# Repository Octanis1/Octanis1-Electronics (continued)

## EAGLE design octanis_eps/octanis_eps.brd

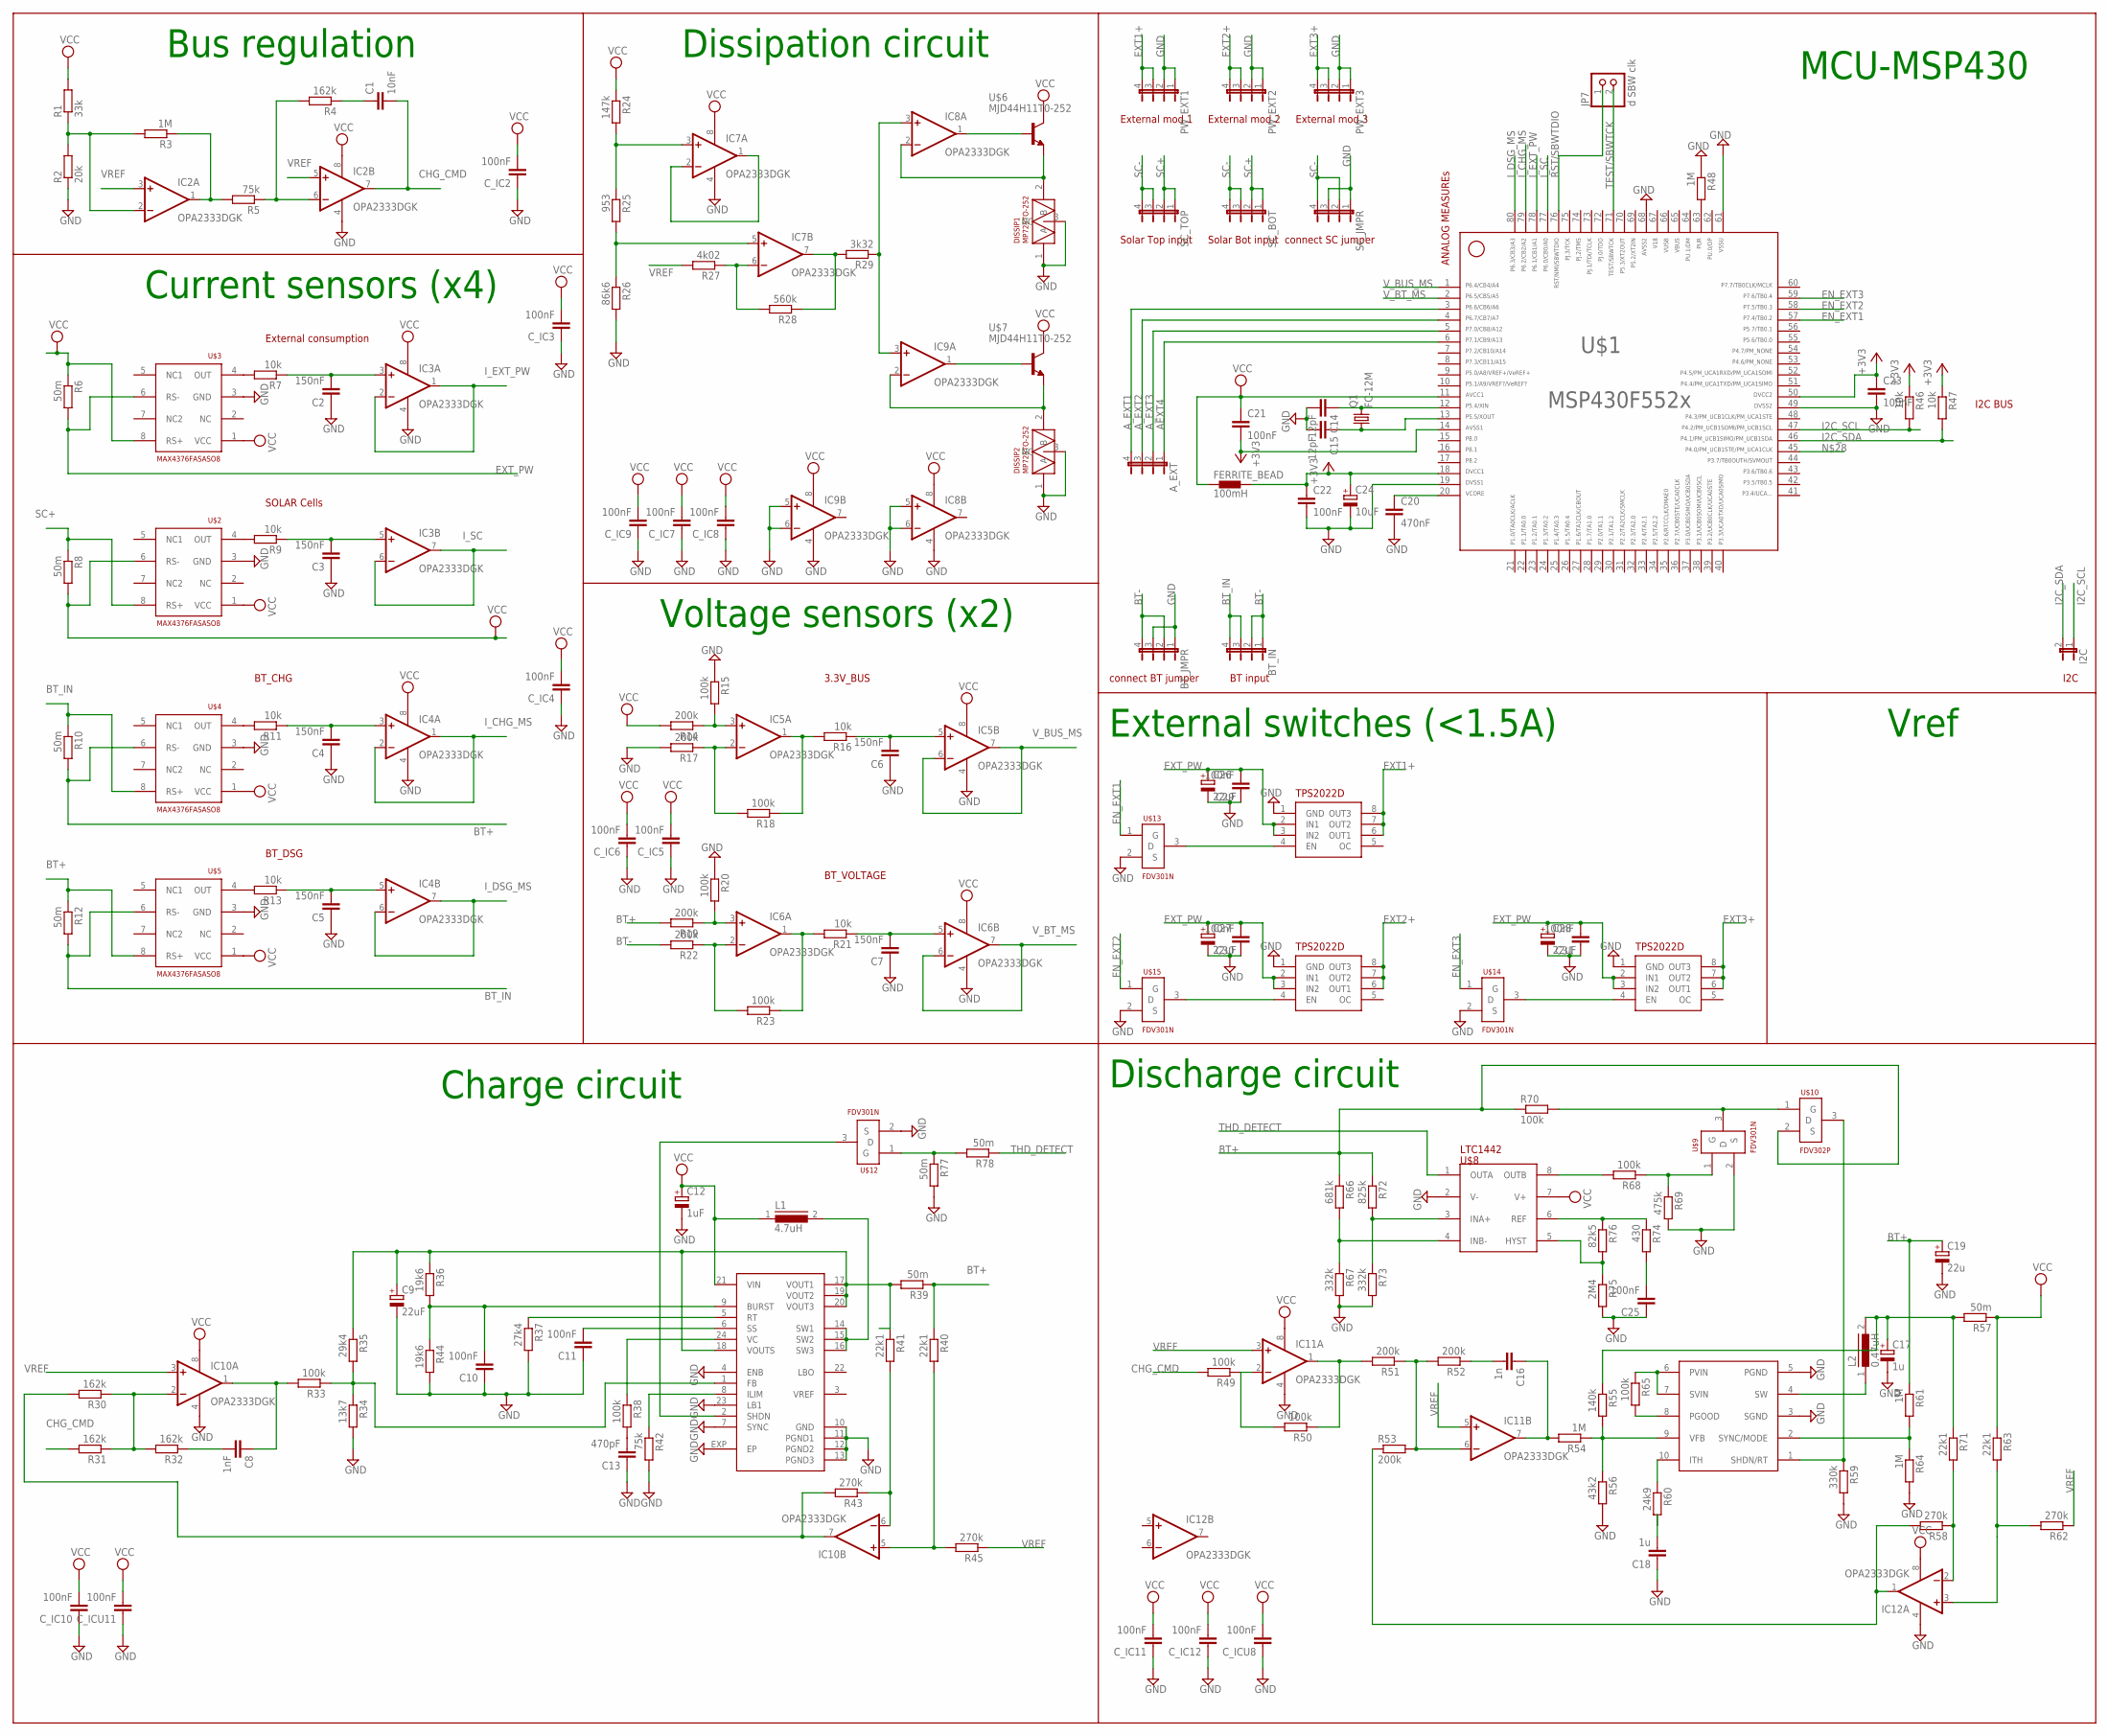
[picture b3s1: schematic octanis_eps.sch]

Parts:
A_EXT: JP4E; JP4
BT_IN: JP4E; JP4
BT_JMPR: JP4E; JP4
C1: 10nF; C0603
C2, C3, C4, C5, C6, C7: 150nF; C0603
C8: 1nF; C0603
C9, C26, C27, C28: 22uF; A/3216-18R
C10, C11, C21, C22, C23, C25, C29, C30, C31: 100nF; C0603
C12: 1uF; A/3216-18R
C13: 470pF; C0603
C14, C15: 12pF; C0603
C16: 1n; C0603
C17: 1u; A/3216-18R
C18: 1u; C0603
C19: 22u; A/3216-18R
C20: 470nF; C0603
C24: 10uF; A/3216-18R
C_IC2, C_IC3, C_IC4, C_IC5, C_IC6, C_IC7, C_IC8, C_IC9, C_IC10, C_IC11, C_IC12: 100nF; C0603
C_ICU8, C_ICU11: 100nF; C0603
DISSIP1, DISSIP2: MP725TO-252; TO252
FERRITE_BEAD: 100mH; 0402
I2C: JP1E; JP1
IC2, IC3, IC4, IC5, IC6, IC7, IC8, IC9, IC10, IC11, IC12: OPA2333DGK; MSOP08
JP7: d SBW clk; 1X02
L1: 4.7uH; DR73
L2: 0.47uH; DR73
LTC3411: LT3411; MSOP10
PW_EXT1, PW_EXT2, PW_EXT3: JP4E; JP4
Q1: FC-12M
R1: 33k; R0603
R2: 20k; R0603
R3, R48, R54, R61, R64: 1M; R0603
R4, R30, R31, R32: 162k; R0603
R5, R42: 75k; R0603
R6, R8, R10, R12, R39, R57, R77, R78: 50m; R0603
R7, R9, R11, R13, R16, R21, R46, R47: 10k; R0603
R14, R17, R19, R22, R51, R52, R53: 200k; R0603
R15, R18, R20, R23, R33, R38, R49, R50, R65, R68, R70: 100k; R0603
R24: 147k; R0603
R25: 953; R0603
R26: 86k6; R0603
R27: 4k02; R0603
R28: 560k; R0603
R29: 3k32; R0603
R34: 13k7; R0603
R35: 29k4; R0603
R36, R44: 19k6; R0603
R37: 27k4; R0603
R40, R41, R63, R71: 22k1; R0603
R43, R45, R58, R62: 270k; R0603
R55: 140k; R0603
R56: 43k2; R0603
R59: 330k; R0603
R60: 24k9; R0603
R66: 681k; R0603
R67, R73: 332k; R0603
R69: 475k; R0603
R72: 825k; R0603
R74: 430; R0603
R75: 2M4; R0603
R76: 82k5; R0603
SC_BOT: JP4E; JP4
SC_JMPR: JP4E; JP4
SC_TOP: JP4E; JP4
U$1: F552X---PN80; PN80
U$2, U$3, U$4, U$5: MAX4376FASASO8; SO8
U$6, U$7: MJD44H11T0-252; TO252
U$8: LTC1442; SO8
U$9, U$12, U$13, U$14, U$15: FDV301N; SOT23
U$10: FDV302P; SOT23
U$11: LTC3421; QFN24
U$16, U$17, U$18: TPS2022D; SO8

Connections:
65: U$1.65
66: U$1.66
67: U$1.67
+3V3: C21.2, C22.1, C23.1, C24.+, FERRITE_BEAD.2, R46.1, R47.1, U$1.14, U$1.18, U$1.50
AEXT4: A_EXT.1, U$1.6
A_EXT1: A_EXT.4, U$1.3
A_EXT2: A_EXT.3, U$1.4
A_EXT3: A_EXT.2, U$1.5
BT+: C19.+, R10.2, R12.1, R19.2, R39.1, R40.1, R61.1, R66.1, R70.1, R72.1, U$4.6 (RS-), U$5.8 (RS+), U$10.2 (S)
BT-: BT_IN.1, BT_IN.2, BT_JMPR.2, BT_JMPR.4, R22.2
BT_IN: BT_IN.3, BT_IN.4, R10.1, R12.2, U$4.8 (RS+), U$5.6 (RS-)
CHG_CMD: C1.2, IC2.7 (OUT), R31.2, R49.2
EN_EXT1: U$1.57, U$13.1 (G)
EN_EXT2: U$1.58, U$15.1 (G)
EN_EXT3: U$1.59, U$14.1 (G)
EXT1+: PW_EXT1.3, PW_EXT1.4, U$16.6 (OUT1), U$16.7 (OUT2), U$16.8 (OUT3)
EXT2+: PW_EXT2.3, PW_EXT2.4, U$17.6 (OUT1), U$17.7 (OUT2), U$17.8 (OUT3)
EXT3+: PW_EXT3.3, PW_EXT3.4, U$18.6 (OUT1), U$18.7 (OUT2), U$18.8 (OUT3)
EXT_PW: C26.+, C27.+, C28.+, C29.2, C30.2, C31.2, R6.2, U$3.6 (RS-), U$16.2 (IN1), U$16.3 (IN2), U$17.2 (IN1), U$17.3 (IN2), U$18.2 (IN1), U$18.3 (IN2)
GND: BT_JMPR.1, BT_JMPR.3, C2.1, C3.1, C4.1, C5.1, C6.1, C7.1, C9.-, C10.1, C11.1, C12.-, C13.1, C14.2, C15.2, C17.-, C18.1, C19.-, C20.2, C22.2, C23.2, C24.-, C25.1, C26.-, C27.-, C28.-, C29.1, C30.1, C31.1, C_IC2.1, C_IC3.1, C_IC4.1, C_IC5.1, C_IC6.1, C_IC7.1, C_IC8.1, C_IC9.1, C_IC10.1, C_IC11.1, C_IC12.1, C_ICU8.1, C_ICU11.1, DISSIP1.1 (A), DISSIP1.3 (NC), DISSIP2.1 (A), DISSIP2.3 (NC), IC2.4 (V-), IC3.4 (V-), IC4.4 (V-), IC5.4 (V-), IC6.4 (V-), IC7.4 (V-), IC8.4 (V-), IC8.5 (+IN), IC8.6 (-IN), IC9.4 (V-), IC9.5 (+IN), IC9.6 (-IN), IC10.4 (V-), IC11.4 (V-), IC12.4 (V-), LTC3411.3 (SGND), LTC3411.5 (PGND), PW_EXT1.1, PW_EXT1.2, PW_EXT2.1, PW_EXT2.2, PW_EXT3.1, PW_EXT3.2, R2.1, R15.1, R17.2, R20.1, R26.2, R34.2, R37.2, R42.2, R44.2, R48.1, R56.2, R59.2, R64.2, R67.2, R69.2, R73.2, R75.2, R77.2, SC_JMPR.1, SC_JMPR.3, U$1.19, U$1.49, U$1.61, U$1.68, U$2.3 (GND), U$3.3 (GND), U$4.3 (GND), U$5.3 (GND), U$8.2 (V-), U$9.2 (S), U$11.4 (ENB), U$11.7 (SYNC), U$11.10 (GND), U$11.11 (PGND1), U$11.12 (PGND2), U$11.13 (PGND3), U$11.23 (LB1), U$11.EXP (EP), U$12.2 (S), U$13.2 (S), U$14.2 (S), U$15.2 (S), U$16.1 (GND), U$17.1 (GND), U$18.1 (GND)
I2C_SCL: I2C.1, R46.2, U$1.47
I2C_SDA: I2C.2, R47.2, U$1.46
I_CHG_MS: IC4.1 (OUT), IC4.2 (-IN), U$1.79
I_DSG_MS: IC4.6 (-IN), IC4.7 (OUT), U$1.80
I_EXT_PW: IC3.1 (OUT), IC3.2 (-IN), U$1.78
I_SC: IC3.6 (-IN), IC3.7 (OUT), U$1.77
unnamed: IC2.2 (-IN), R1.1, R2.2, R3.2
unnamed: IC2.1 (OUT), R3.1, R5.2
unnamed: C1.1, R4.1
unnamed: IC2.6 (-IN), R4.2, R5.1
unnamed: C4.2, IC4.3 (+IN), R11.1
unnamed: C2.2, IC3.3 (+IN), R7.1
unnamed: C3.2, IC3.5 (+IN), R9.1
unnamed: C5.2, IC4.5 (+IN), R13.1
unnamed: C7.2, IC6.5 (+IN), R21.1
unnamed: IC6.1 (OUT), R21.2, R23.1
unnamed: C6.2, IC5.5 (+IN), R16.1
unnamed: IC5.1 (OUT), R16.2, R18.1
unnamed: IC5.2 (-IN), R17.1, R18.2
unnamed: IC5.3 (+IN), R14.1, R15.2
unnamed: IC6.2 (-IN), R22.1, R23.2
unnamed: IC6.3 (+IN), R19.1, R20.2
unnamed: IC7.1 (OUT), IC7.2 (-IN)
unnamed: IC7.3 (+IN), R24.2, R25.1
unnamed: IC7.5 (+IN), R25.2, R26.1
unnamed: IC7.6 (-IN), R27.1, R28.2
unnamed: IC7.7 (OUT), R28.1, R29.2
unnamed: IC8.3 (+IN), IC9.3 (+IN), R29.1
unnamed: IC10.2 (-IN), R30.1, R31.1, R32.2
unnamed: C8.2, R32.1
unnamed: C8.1, IC10.1 (OUT), R33.2
unnamed: R33.1, R34.1, R35.2, U$11.1 (FB)
unnamed: R48.2, U$1.63
unnamed: R42.1, U$11.8 (ILIM)
unnamed: C10.2, R36.2, R44.1, U$11.9 (BURST)
unnamed: C13.2, R38.2
unnamed: R37.1, U$11.5 (RT)
unnamed: C11.2, U$11.6 (SS)
unnamed: U$15.3 (D), U$17.4 (EN)
unnamed: U$11.2 (SHDN), U$12.3 (D)
unnamed: IC10.5 (+IN), R40.2, R45.2
unnamed: IC10.6 (-IN), R41.2, R43.1
unnamed: R9.2, U$2.4 (OUT)
unnamed: R11.2, U$4.4 (OUT)
unnamed: R7.2, U$3.4 (OUT)
unnamed: R13.2, U$5.4 (OUT)
unnamed: IC8.1 (OUT), U$6.1 (B)
unnamed: IC9.1 (OUT), U$7.1 (B)
unnamed: DISSIP2.2 (B), IC9.2 (-IN), U$7.3 (E)
unnamed: DISSIP1.2 (B), IC8.2 (-IN), U$6.3 (E)
unnamed: C14.1, Q1.2, U$1.12
unnamed: C20.1, U$1.20
unnamed: C15.1, Q1.1, U$1.13
unnamed: C16.1, IC11.7 (OUT), R54.2
unnamed: IC11.2 (-IN), R49.1, R50.2
unnamed: IC11.1 (OUT), R50.1, R51.2
unnamed: IC11.6 (-IN), R51.1, R52.2, R53.2
unnamed: C16.2, R52.1
unnamed: IC12.1 (OUT), R53.1, R58.2
unnamed: LTC3411.9 (VFB), R54.1, R55.2, R56.1
unnamed: C17.+, L2.2, R55.1, R57.2, R71.1
unnamed: LTC3411.10 (ITH), R60.1
unnamed: LTC3411.2 (SYNC/MODE), R61.2, R64.1
unnamed: IC12.2 (-IN), R58.1, R71.2
unnamed: IC12.3 (+IN), R62.2, R63.2
unnamed: LTC3411.8 (PGOOD), R65.2
unnamed: LTC3411.6 (PVIN), LTC3411.7 (SVIN), R65.1
unnamed: LTC3411.1 (SHDN/RT), R59.1, U$10.3 (D)
unnamed: R66.2, R67.1, U$8.4 (INB-)
unnamed: R68.2, U$8.8 (OUTB)
unnamed: R68.1, R69.1, U$9.1 (G)
unnamed: R72.2, R73.1, U$8.3 (INA+)
unnamed: R70.2, U$9.3 (D), U$10.1 (G)
unnamed: R74.1, R76.1, U$8.6 (REF)
unnamed: R75.1, R76.2, U$8.5 (HYST)
unnamed: C25.2, R74.2
unnamed: C9.+, R35.1, R36.1, R39.2, U$11.17 (VOUT1), U$11.18 (VOUTS), U$11.19 (VOUT2), U$11.20 (VOUT3)
unnamed: R77.1, R78.2, U$12.1 (G)
unnamed: L2.1, LTC3411.4 (SW)
unnamed: L1.2, U$11.14 (SW1), U$11.15 (SW2), U$11.16 (SW3)
unnamed: U$13.3 (D), U$16.4 (EN)
unnamed: U$14.3 (D), U$18.4 (EN)
RST/SBWTDIO: JP7.1, U$1.76
SC+: R8.1, SC_BOT.1, SC_BOT.2, SC_TOP.1, SC_TOP.2, U$2.8 (RS+)
SC-: SC_BOT.3, SC_BOT.4, SC_JMPR.2, SC_JMPR.4, SC_TOP.3, SC_TOP.4
TEST/SBWTCK: JP7.2, U$1.71
THD_DETECT: R78.1, U$8.1 (OUTA)
UUU: IC10.7 (OUT), R30.2, R43.2
VCC: C12.+, C21.1, C_IC2.2, C_IC3.2, C_IC4.2, C_IC5.2, C_IC6.2, C_IC7.2, C_IC8.2, C_IC9.2, C_IC10.2, C_IC11.2, C_IC12.2, C_ICU8.2, C_ICU11.2, FERRITE_BEAD.1, IC2.8 (V+), IC3.8 (V+), IC4.8 (V+), IC5.8 (V+), IC6.8 (V+), IC7.8 (V+), IC8.8 (V+), IC9.8 (V+), IC10.8 (V+), IC11.8 (V+), IC12.8 (V+), L1.1, R1.2, R6.1, R8.2, R14.2, R24.1, R57.1, R63.1, U$1.11, U$2.1 (VCC), U$2.6 (RS-), U$3.1 (VCC), U$3.8 (RS+), U$4.1 (VCC), U$5.1 (VCC), U$6.2 (C), U$7.2 (C), U$8.7 (V+), U$11.21 (VIN)
VREF: IC2.3 (+IN), IC2.5 (+IN), IC10.3 (+IN), IC11.3 (+IN), IC11.5 (+IN), R27.2, R45.1, R62.1
V_BT_MS: IC6.6 (-IN), IC6.7 (OUT), U$1.2
V_BUS_MS: IC5.6 (-IN), IC5.7 (OUT), U$1.1

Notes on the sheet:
Bus regulation
Vref
Current sensors (x4)
SOLAR Cells
3.3V_BUS
Charge circuit
Discharge circuit
External switches (<1.5A)
MCU-MSP430
BT_CHG
BT_DSG
Voltage sensors (x2)
BT_VOLTAGE
Dissipation circuit
I2C BUS
ANALOG MEASUREs
connect BT jumper
BT input
Solar Bot input
Solar Top input
External mod 2
External mod 1
I2C
External mod 3
External consumption
connect SC jumper

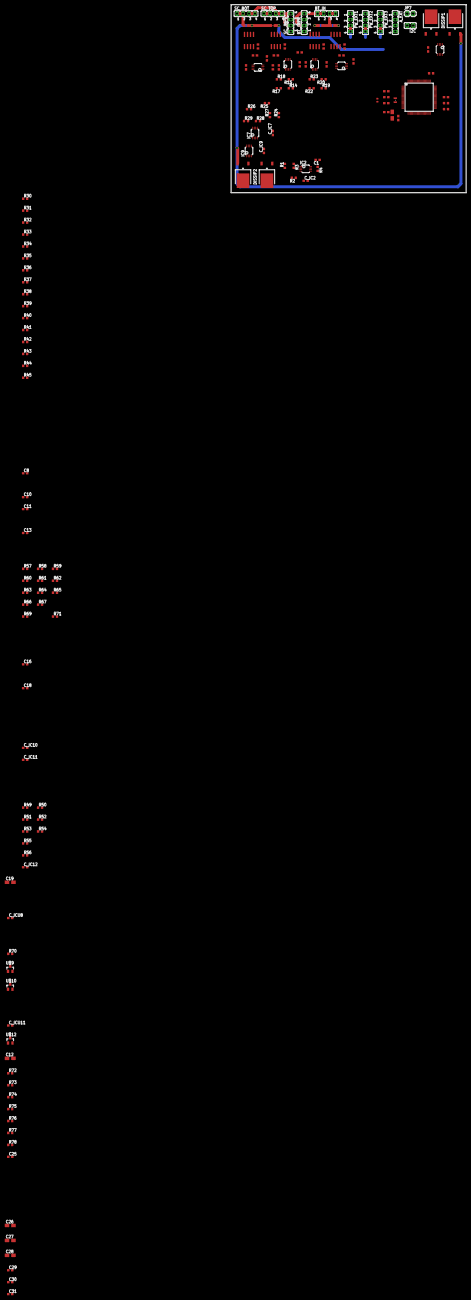
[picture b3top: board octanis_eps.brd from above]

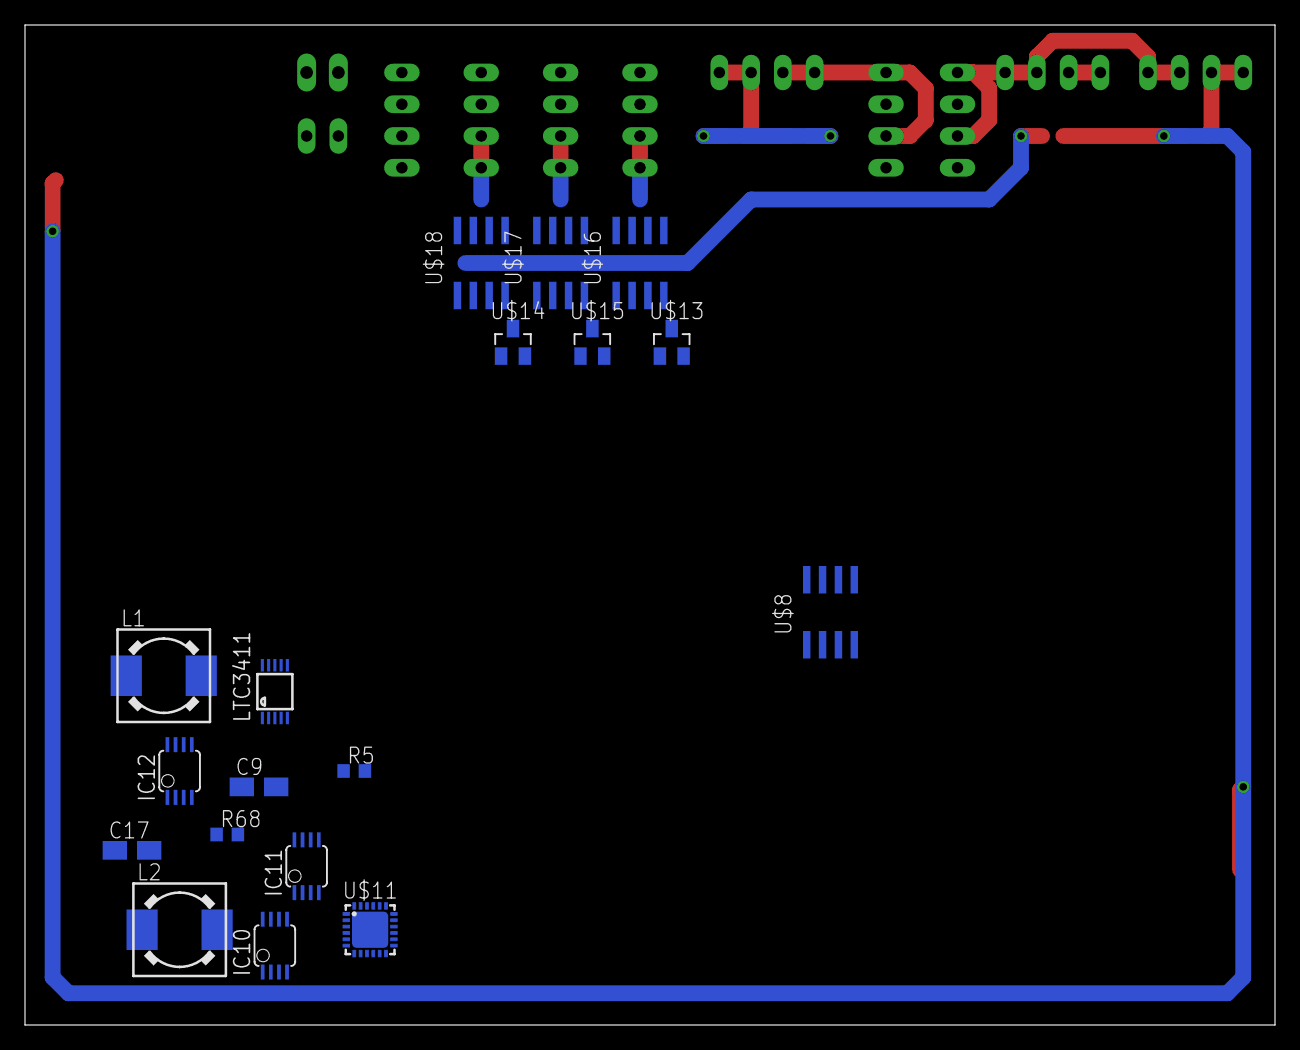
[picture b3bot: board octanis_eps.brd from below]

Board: 2 copper layers, 100.0 x 80.0 mm, 169 parts (18 on the bottom side), 109 nets.

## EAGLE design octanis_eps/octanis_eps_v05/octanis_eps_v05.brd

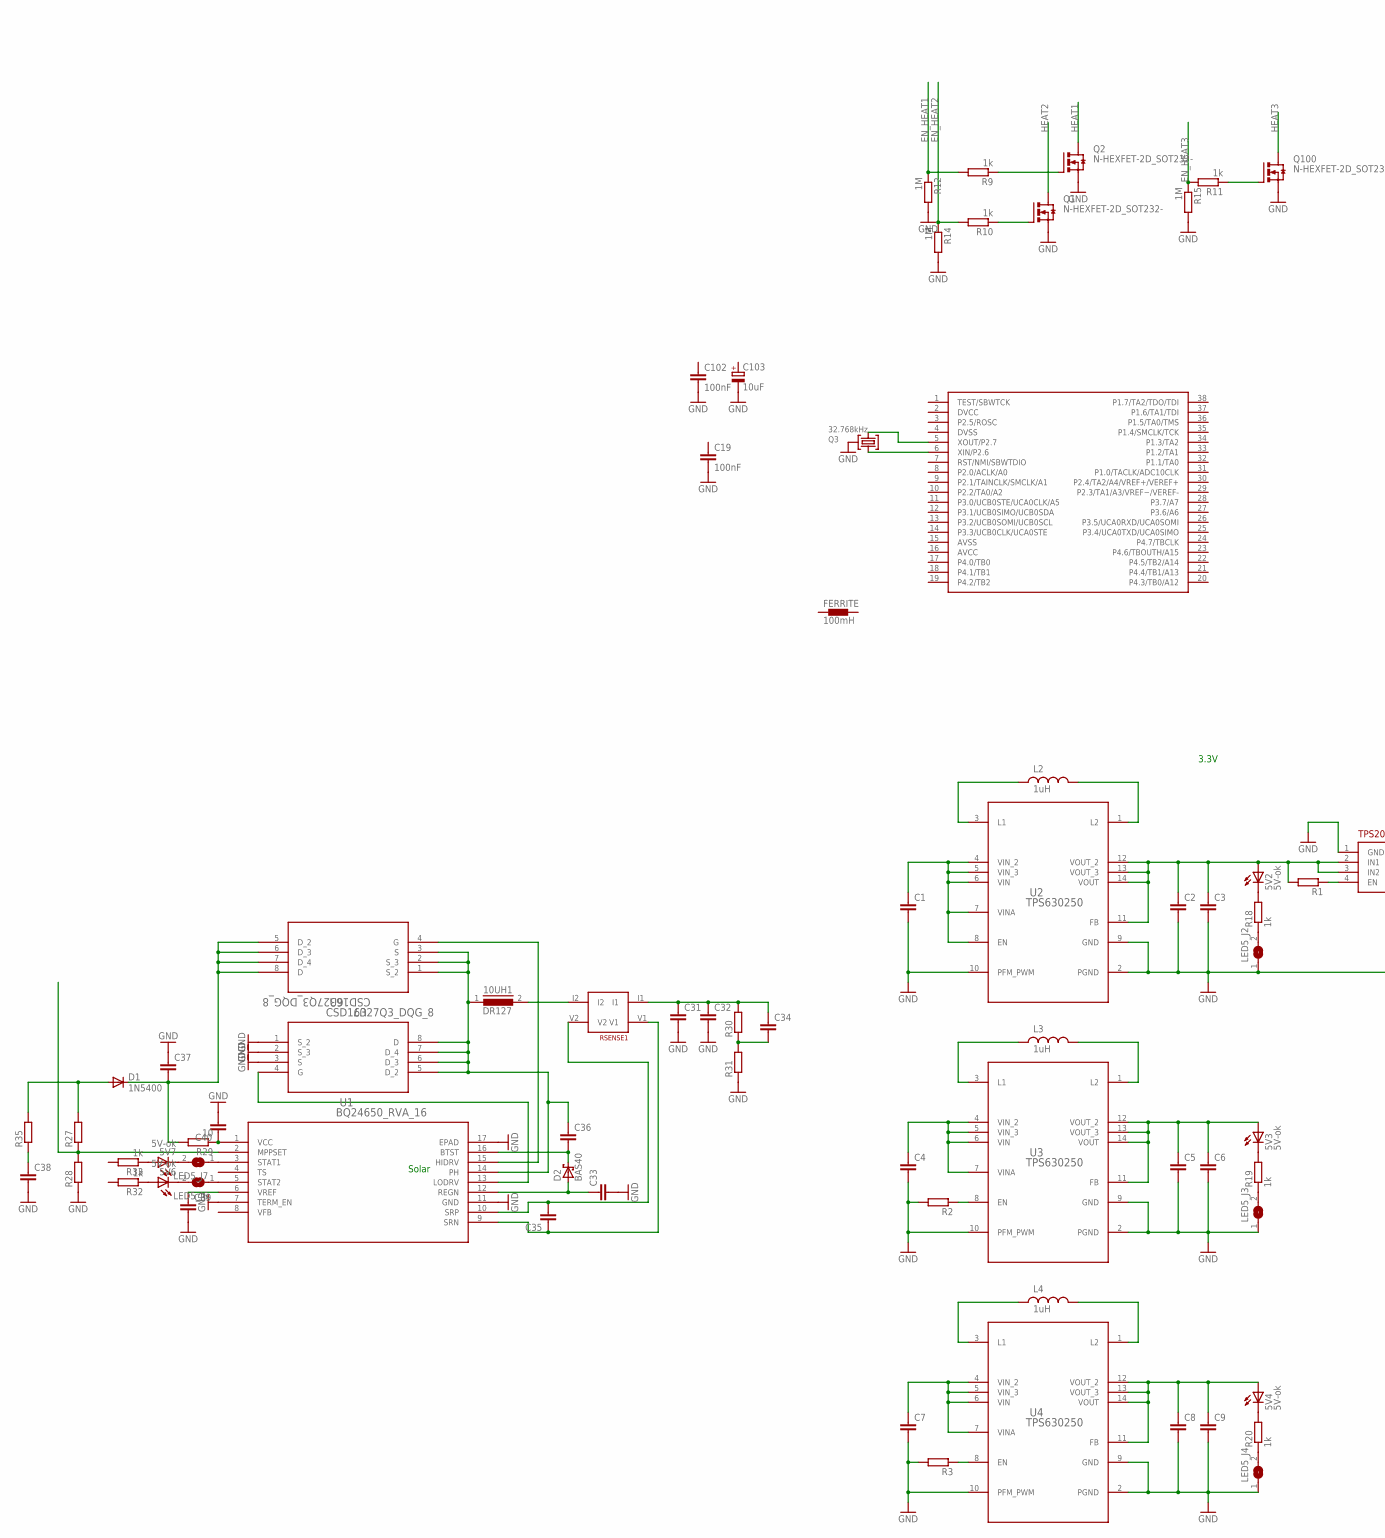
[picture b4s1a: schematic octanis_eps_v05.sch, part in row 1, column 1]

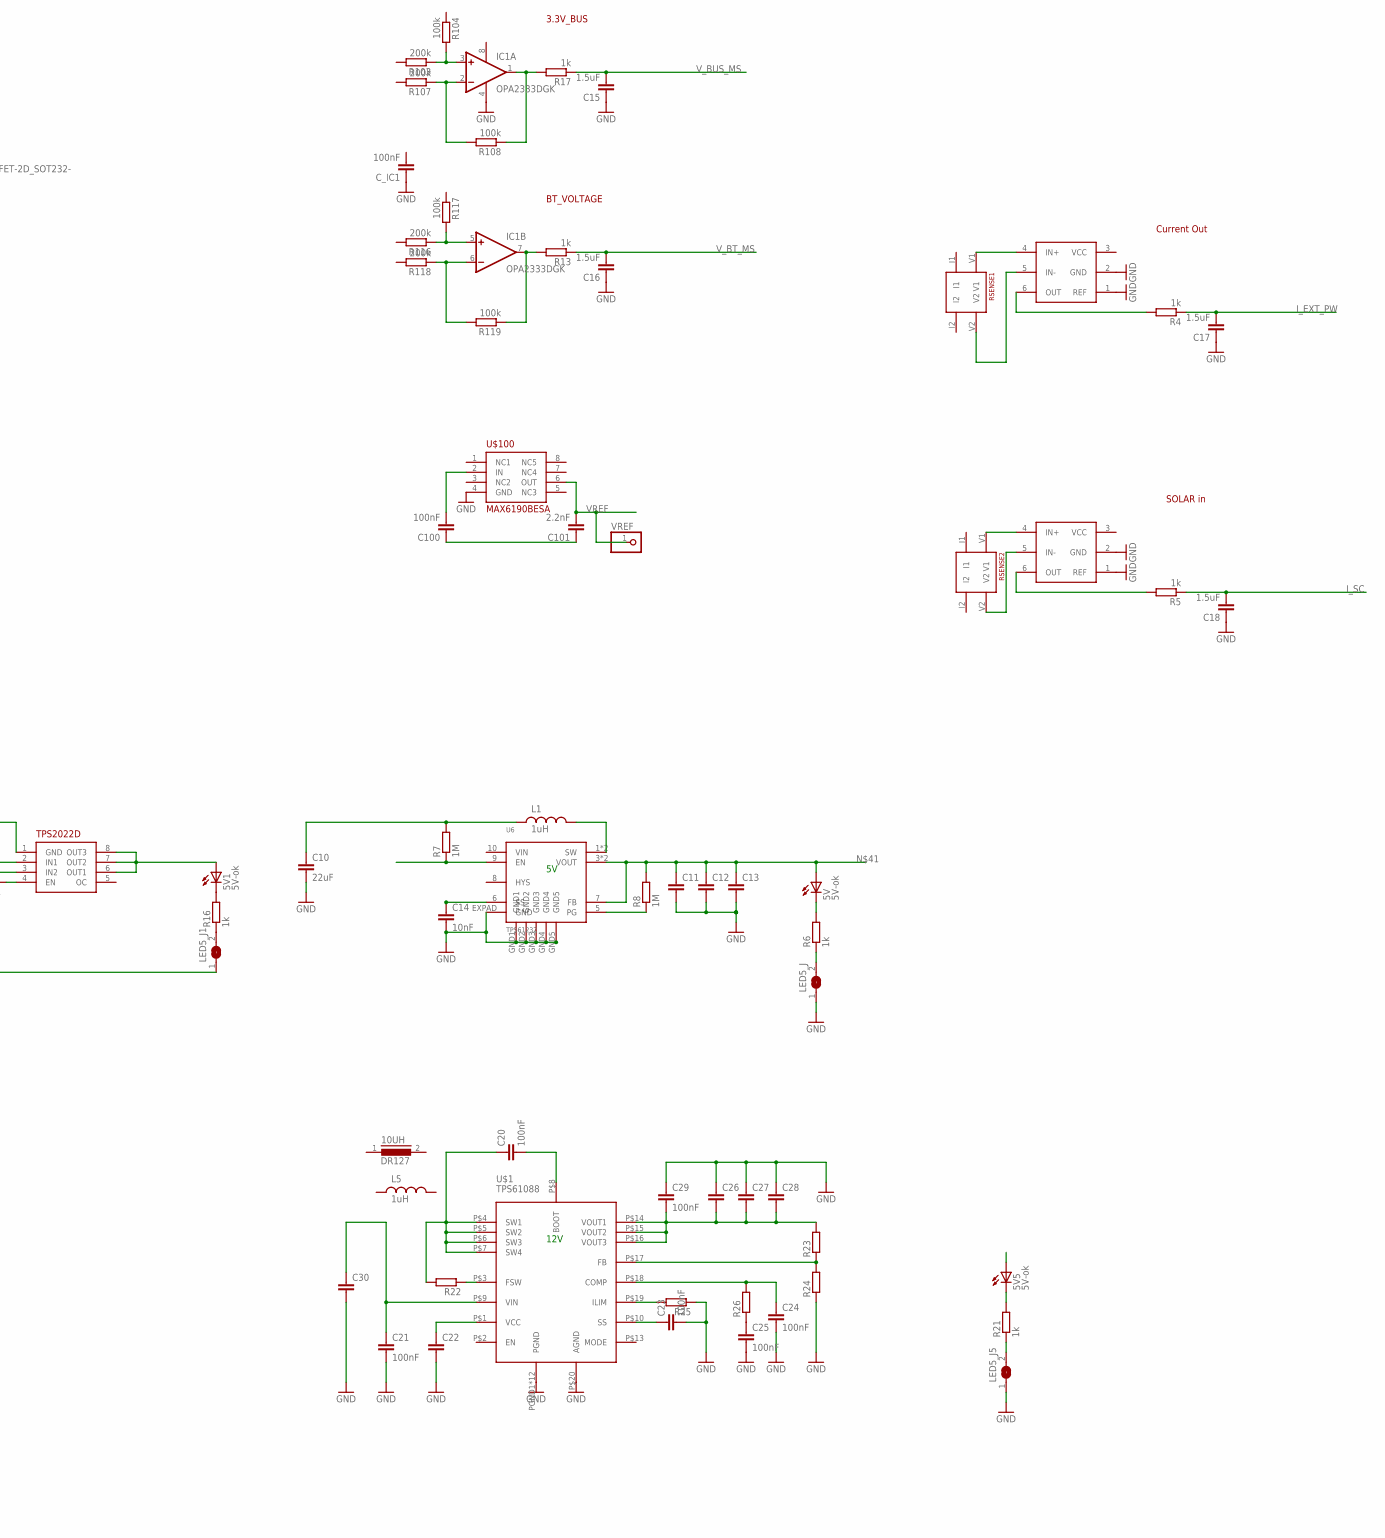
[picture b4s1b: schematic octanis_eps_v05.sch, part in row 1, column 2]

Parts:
5V, 5V1, 5V2, 5V3, 5V4, 5V5, 5V6, 5V7: 5V-ok; CHIPLED_0603
10UH, 10UH1: DR127
C1, C2, C3, C4, C5, C6, C7, C8, C9, C11, C12, C13, C26, C27, C28, C30, C31, C32, C37: C-EUC0805; C0805
C10: 22uF; C0603
C14: 10nF; C0603
C15, C16, C17, C18: 1.5uF; C0603
C19, C20, C21, C23, C24, C25, C29, C100, C102: 100nF; C0603
C22, C33, C34, C35, C36, C38, C39, C40: C-EUC0603; C0603
C101: 2.2nF; C0603
C103: 10uF; A/3216-18R
C_IC1: 100nF; C0603
D1: 1N5400; DO201-15
D2: BAS40; SOT23
FERRITE: 100mH; 0402
IC1: OPA2333DGK; MSOP08
L1, L2, L3, L4, L5: 1uH; XFL4020
LED5_J, LED5_J1, LED5_J2, LED5_J3, LED5_J4, LED5_J5, LED5_J6, LED5_J7: SJ
Q1, Q2, Q100: N-HEXFET-2D_SOT232-; SOT223
Q3: 32.768kHz; MS3V-T1R
R1, R2, R3, R22, R23, R24, R25, R26, R27, R28, R30, R31, R35: R-EU_R0603; R0603
R4, R5, R6, R9, R10, R11, R13, R16, R17, R18, R19, R20, R21, R32, R33: 1k; R0603
R7, R8, R12, R14, R15: 1M; R0603
R29: 10; R0603
R103, R107, R116, R118: 200k; R0603
R104, R108, R117, R119: 100k; R0603
RSENSE1: RSENSE2; 4PADS_RESISTOR
R_SENSE1, R_SENSE2: RSENSE1; 4PADS_RESISTOR
U1: BQ24650_RVA_16; RVA16_2P14X2P14
U2, U3, U4: TPS630250; RNC0014A
U5: TPS2022D; SO8
U6: TPS61232; S-PVSON-N10
U7, U9: CSD16327Q3_DQG_8; DQG8
U8: MSP430G2544; TSSOP38_MSPGXX44_SERIES
U$1: TPS61088; R-PVQFN-N20
U$2, U$3: INA213; SC70-6
U$100: MAX6190BESA; SO8
VREF: PINHD-1X1; 1X01

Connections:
+5V5: 5V5.A
EN_HEAT1: R9.2, R12.1
EN_HEAT2: R10.2, R14.1
EN_HEAT3: R11.2, R15.1
GND: C1.2, C2.2, C3.2, C4.2, C5.2, C6.2, C7.2, C8.2, C9.2, C10.2, C11.2, C12.2, C13.2, C14.2, C15.1, C16.1, C17.1, C18.1, C19.2, C21.2, C22.2, C23.2, C24.2, C25.2, C26.1, C27.1, C28.1, C29.1, C30.2, C31.2, C32.2, C33.2, C37.1, C38.2, C39.2, C40.2, C102.2, C103.-, C_IC1.1, IC1.4 (V-), LED5_J.1, LED5_J1.1, LED5_J2.1, LED5_J3.1, LED5_J4.1, LED5_J5.1, Q1.3 (S), Q2.3 (S), Q3.P3 (GND), Q100.3 (S), R2.2, R3.2, R12.2, R14.2, R15.2, R24.1, R25.1, R28.1, R31.1, U1.7 (TERM_EN), U1.11 (GND), U1.17 (EPAD), U2.2 (PGND), U2.9 (GND), U2.10 (PFM_PWM), U3.2 (PGND), U3.9 (GND), U3.10 (PFM_PWM), U4.2 (PGND), U4.9 (GND), U4.10 (PFM_PWM), U5.1 (GND), U6.EXPAD (GND), U6.GND1, U6.GND2, U6.GND3, U6.GND4, U6.GND5, U9.1 (S_2), U9.2 (S_3), U9.3 (S), U$1.P$20 (AGND), U$1.PGND1 (PGND), U$1.PGND2 (PGND), U$1.PGND3 (PGND), U$1.PGND4 (PGND), U$1.PGND5 (PGND), U$1.PGND6 (PGND), U$1.PGND7 (PGND), U$1.PGND8 (PGND), U$1.PGND9 (PGND), U$1.PGND10 (PGND), U$1.PGND11 (PGND), U$1.PGND12 (PGND), U$2.1 (REF), U$2.2 (GND), U$3.1 (REF), U$3.2 (GND), U$100.4 (GND)
HEAT1: Q2.2 (D), Q2.4 (D)
HEAT2: Q1.2 (D), Q1.4 (D)
HEAT3: Q100.2 (D), Q100.4 (D)
IND: L1.P$2 (2), U6.1 (SW), U6.2 (SW)
I_EXT_PW: C17.2, R4.1
I_SC: C18.2, R5.1
unnamed: L2.P$1 (1), U2.3 (L1)
unnamed: R8.1, U6.5 (PG)
unnamed: L2.P$2 (2), U2.1 (L2)
unnamed: C1.1, U2.4 (VIN_2), U2.5 (VIN_3), U2.6 (VIN), U2.7 (VINA), U2.8 (EN)
unnamed: R1.1, U5.4 (EN)
unnamed: L3.P$1 (1), U3.3 (L1)
unnamed: L3.P$2 (2), U3.1 (L2)
unnamed: 5V1.A, U5.6 (OUT1), U5.7 (OUT2), U5.8 (OUT3)
unnamed: C4.1, U3.4 (VIN_2), U3.5 (VIN_3), U3.6 (VIN), U3.7 (VINA)
unnamed: R2.1, U3.8 (EN)
unnamed: L4.P$1 (1), U4.3 (L1)
unnamed: L4.P$2 (2), U4.1 (L2)
unnamed: C7.1, U4.4 (VIN_2), U4.5 (VIN_3), U4.6 (VIN), U4.7 (VINA)
unnamed: LED5_J.2, R6.1
unnamed: R3.1, U4.8 (EN)
unnamed: 5V3.A, C5.1, C6.1, U3.11 (FB), U3.12 (VOUT_2), U3.13 (VOUT_3), U3.14 (VOUT)
unnamed: 5V4.A, C8.1, C9.1, U4.11 (FB), U4.12 (VOUT_2), U4.13 (VOUT_3), U4.14 (VOUT)
unnamed: 5V2.A, C2.1, C3.1, R1.2, U2.11 (FB), U2.12 (VOUT_2), U2.13 (VOUT_3), U2.14 (VOUT), U5.2 (IN1), U5.3 (IN2)
unnamed: IC1.1 (OUT), R17.2, R108.1
unnamed: IC1.2 (-IN), R107.1, R108.2
unnamed: IC1.3 (+IN), R103.1, R104.2
unnamed: IC1.7 (OUT), R13.2, R119.1
unnamed: IC1.6 (-IN), R118.1, R119.2
unnamed: IC1.5 (+IN), R116.1, R117.2
unnamed: R4.2, U$3.6 (OUT)
unnamed: R5.2, U$2.6 (OUT)
unnamed: Q2.1 (G), R9.1
unnamed: C100.2, U$100.2 (IN)
unnamed: C100.1, C101.1
unnamed: Q3.P1 (1), U8.6 (XIN/P2.6)
unnamed: Q1.1 (G), R10.1
unnamed: R_SENSE1.V1, U$3.4 (IN+)
unnamed: R_SENSE1.V2, U$3.5 (IN-)
unnamed: RSENSE1.V1, U$2.4 (IN+)
unnamed: RSENSE1.V2, U$2.5 (IN-)
unnamed: Q3.P2 (2), U8.5 (XOUT/P2.7)
unnamed: Q100.1 (G), R11.1
unnamed: C20.2, U$1.P$8 (BOOT)
unnamed: 5V1.C, R16.2
unnamed: LED5_J1.2, R16.1
unnamed: 5V.A, C11.1, C12.1, C13.1, R8.2, U6.3 (VOUT), U6.4 (VOUT), U6.7 (FB)
unnamed: C14.1, U6.6 (SS)
unnamed: 5V2.C, R18.2
unnamed: 5V.C, R6.2
unnamed: LED5_J2.2, R18.1
unnamed: 5V4.C, R20.2
unnamed: LED5_J4.2, R20.1
unnamed: 5V5.C, R21.2
unnamed: LED5_J5.2, R21.1
unnamed: C20.1, R22.2, U$1.P$4 (SW1), U$1.P$5 (SW2), U$1.P$6 (SW3), U$1.P$7 (SW4)
unnamed: 5V3.C, R19.2
unnamed: LED5_J3.2, R19.1
unnamed: R22.1, U$1.P$3 (FSW)
unnamed: C25.1, R26.1
unnamed: R7.1, U6.9 (EN)
unnamed: C23.1, U$1.P$10 (SS)
unnamed: R25.2, U$1.P$19 (ILIM)
unnamed: C24.1, R26.2, U$1.P$18 (COMP)
unnamed: C22.1, U$1.P$1 (VCC)
unnamed: R23.1, R24.2, U$1.P$17 (FB)
unnamed: C26.2, C27.2, C28.2, C29.2, R23.2, U$1.P$14 (VOUT1), U$1.P$15 (VOUT2), U$1.P$16 (VOUT3)
unnamed: C21.1, C30.1, U$1.P$9 (VIN)
unnamed: C10.1, L1.P$1 (1), R7.2
unnamed: R27.1, R28.2, U1.2 (MPPSET)
unnamed: C38.1, R35.1
unnamed: 5V7.A, R33.1
unnamed: 5V6.C, LED5_J6.2
unnamed: 5V7.C, LED5_J7.2
unnamed: 5V6.A, R32.1
unnamed: LED5_J6.1, U1.5 (STAT2)
unnamed: LED5_J7.1, U1.3 (STAT1)
unnamed: C39.1, U1.6 (VREF)
unnamed: C40.1, R29.1, U1.1 (VCC)
unnamed: D1.A, R27.2, R35.2
unnamed: C37.2, D1.C, R29.2, U7.5 (D_2), U7.6 (D_3), U7.7 (D_4), U7.8 (D)
unnamed: 10UH1.1, C36.1, U1.14 (PH), U7.1 (S_2), U7.2 (S_3), U7.3 (S), U9.5 (D_2), U9.6 (D_3), U9.7 (D_4), U9.8 (D)
unnamed: C35.2, R_SENSE2.V2, U1.10 (SRP)
unnamed: C35.1, R_SENSE2.V1, U1.9 (SRN)
unnamed: 10UH1.2, R_SENSE2.I2
unnamed: U1.15 (HIDRV), U7.4 (G)
unnamed: U1.13 (LODRV), U9.4 (G)
unnamed: C34.2, R30.1, R31.2
unnamed: C31.1, C32.1, C34.1, R30.2, R_SENSE2.I1
unnamed: C33.1, D2.1 (A), U1.12 (REGN)
unnamed: C36.2, D2.3 (C), U1.16 (BTST)
V+: IC1.8 (V+)
VREF: C101.2, U$100.6 (OUT), VREF.1
V_BT_MS: C16.2, R13.1
V_BUS_MS: C15.2, R17.1

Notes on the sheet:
Solar
3.3V
12V
3.3V_BUS
BT_VOLTAGE
SOLAR in
Current Out

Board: 2 copper layers, 135 parts (0 on the bottom side), 98 nets, no tracks yet.
